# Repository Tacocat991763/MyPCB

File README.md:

# Screaminbanana's Starbie!
This is my submission to Week 1 of the Hack Club YSWS Half Life.
This is a small circuit board with the capability to detect button presses, movement, and environment temp/humidity. 
To make it I followed the guide on Half Life, I also strayed from it sometimes, but it's mostly a starbie.
You can find the BOM in the repo: [BOM.md](BOM.md).
If you would like to see my journal as I made this incredible piece of technology, please check out [JOURNAL.md](JOURNAL.md).
Anyway, here are some photos of the design:

If you decide to make this, I hope you like it!

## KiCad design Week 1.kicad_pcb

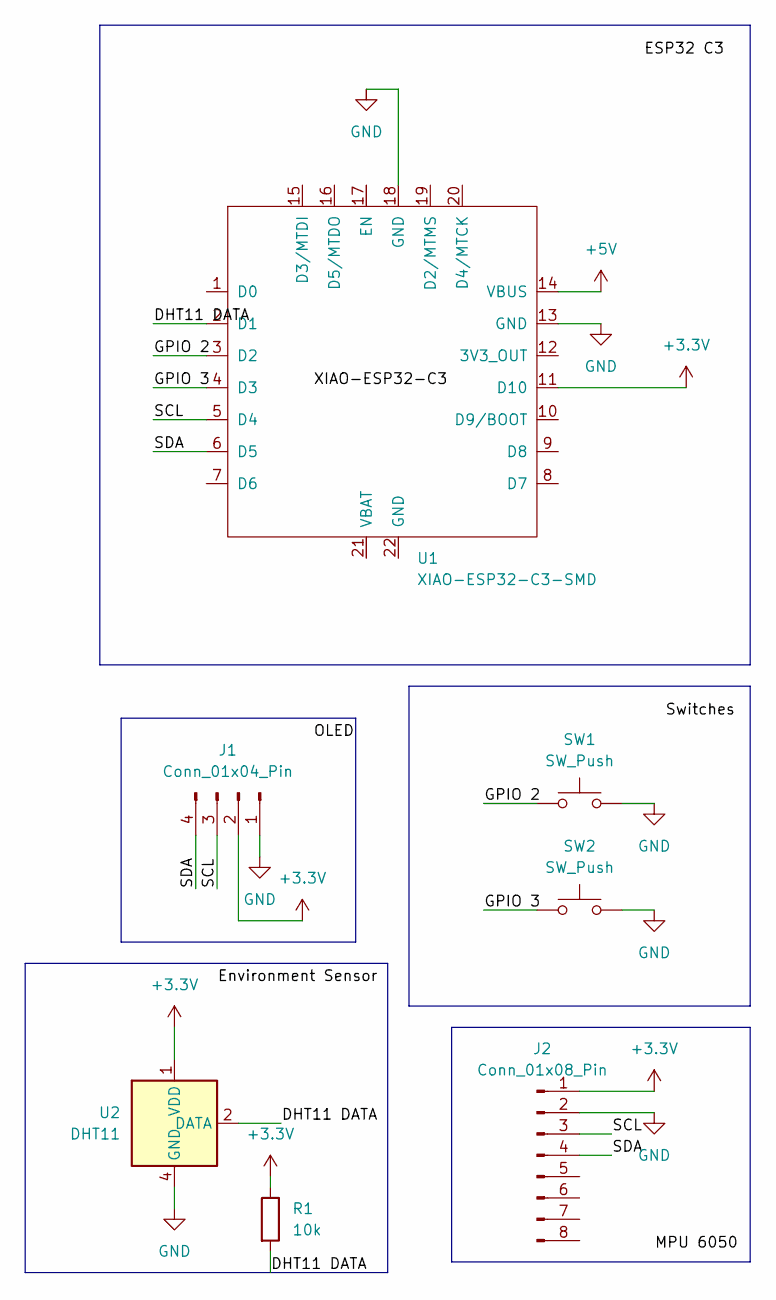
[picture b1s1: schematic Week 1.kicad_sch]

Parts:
J1: Conn_01x04_Pin; Display_128x64_096_I2C
J2: Conn_01x08_Pin; PinHeader_1x08_P2.54mm_Vertical
R1: 10k; R_Axial_DIN0204_L3.6mm_D1.6mm_P7.62mm_Horizontal
SW1, SW2: SW_Push; SW_Cherry_MX_1.00u_PCB
U1: XIAO-ESP32-C3-SMD
U2: DHT11; Aosong_DHT11_5.5x12.0_P2.54mm

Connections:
+3.3V: J1.2, J2.1, R1.1, U1.11 (D10), U2.1 (VDD)
+5V: U1.14 (VBUS)
/DHT11 DATA: R1.2, U1.2 (D1), U2.2 (DATA)
/GPIO 2: SW1.1, U1.3 (D2)
/GPIO 3: SW2.1, U1.4 (D3)
/SCL: J1.3, J2.3, U1.5 (D4)
/SDA: J1.4, J2.4, U1.6 (D5)
GND: J1.1, J2.2, SW1.2, SW2.2, U1.13 (GND), U1.18 (GND), U2.4 (GND)

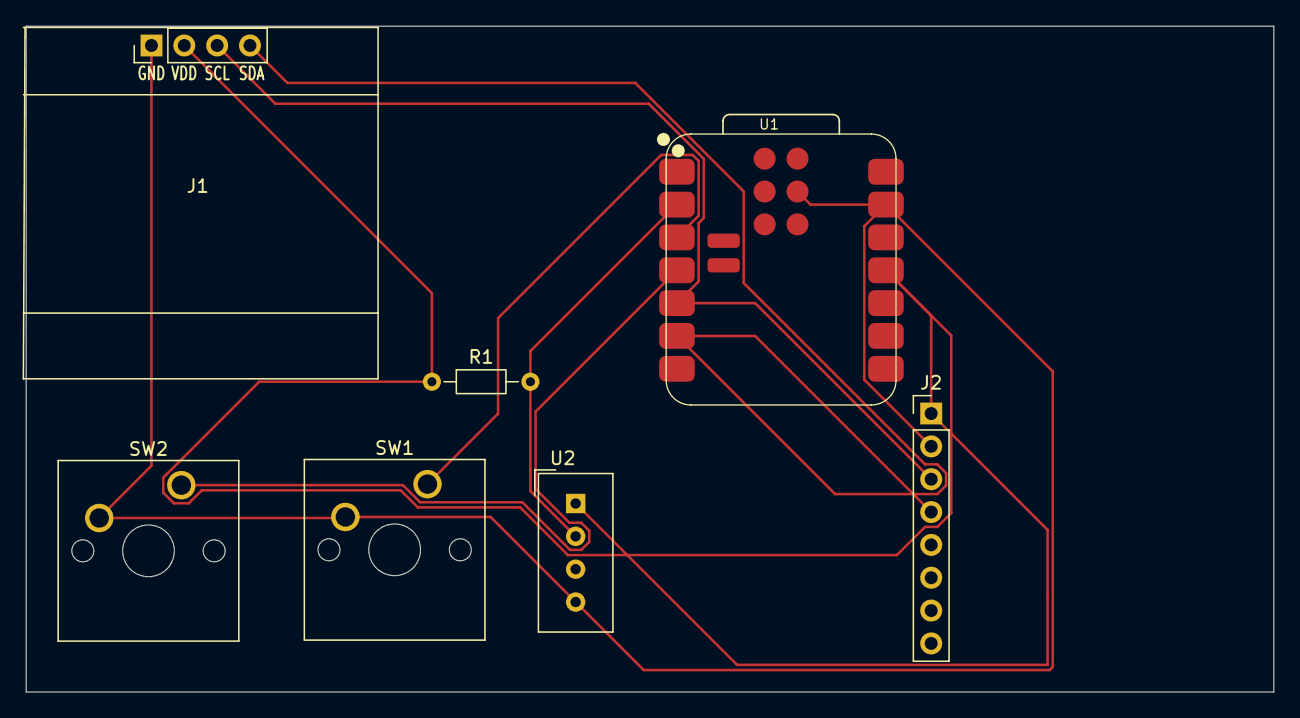
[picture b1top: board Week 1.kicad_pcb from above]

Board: 2 copper layers, 96.5 x 51.5 mm, 7 parts (0 on the bottom side), 7 nets.
